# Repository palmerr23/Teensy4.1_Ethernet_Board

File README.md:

# Teensy4.1_Ethernet_Board
A HandRun HR91105A MagJack board for Teensy 4.1 Ethernet

Board files are KiCAD 6.0

Gerbers should be OK for most PCB manufacturers. Note there are no ground planes.

The CASE pad should be connected to chassis ground, if one exists. Do not connect the CASE pad to Teensy GND. 

## Design is still to be tested (awaiting PCBs).

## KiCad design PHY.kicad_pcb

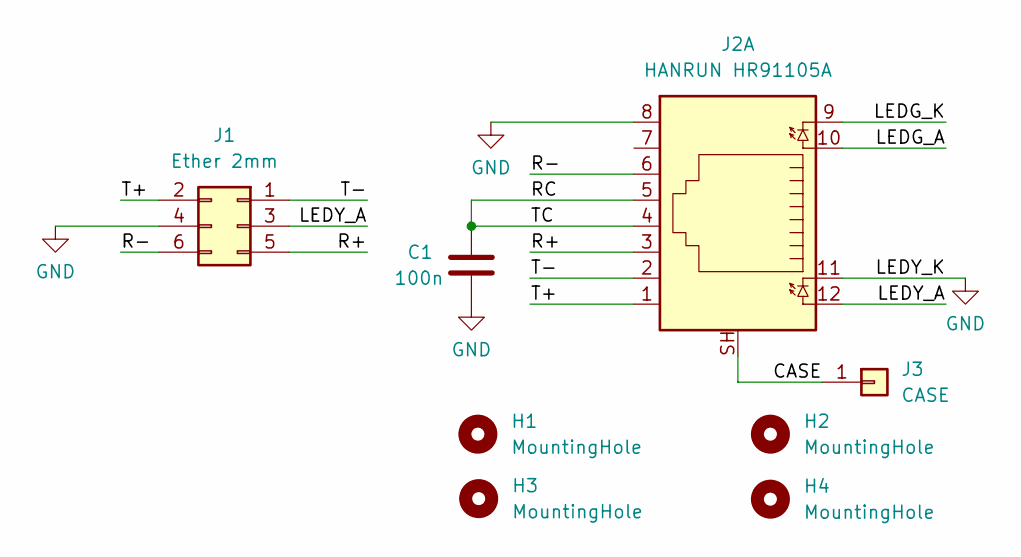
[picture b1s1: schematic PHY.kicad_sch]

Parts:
C1: 100n; C_0805_2012Metric_Pad1.18x1.45mm_HandSolder
H1, H2, H3, H4: MountingHole; MountingHole_3.5mm
J1: Ether 2mm; PinHeader_2x03_P2.00mm_Vertical
J2: HANRUN HR91105A; RJ45_Hanrun_HR911105A
J3: CASE; 1X01

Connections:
/CASE: J2.SH, J3.1
/LEDG_A: J2.10
/LEDG_K: J2.9
/LEDY_A: J1.3, J2.12
/R+: J1.5, J2.3
/R-: J1.6, J2.6
/RC: C1.1, J2.4, J2.5
/T+: J1.2, J2.1
/T-: J1.1, J2.2
GND: C1.2, J1.4, J2.8, J2.11

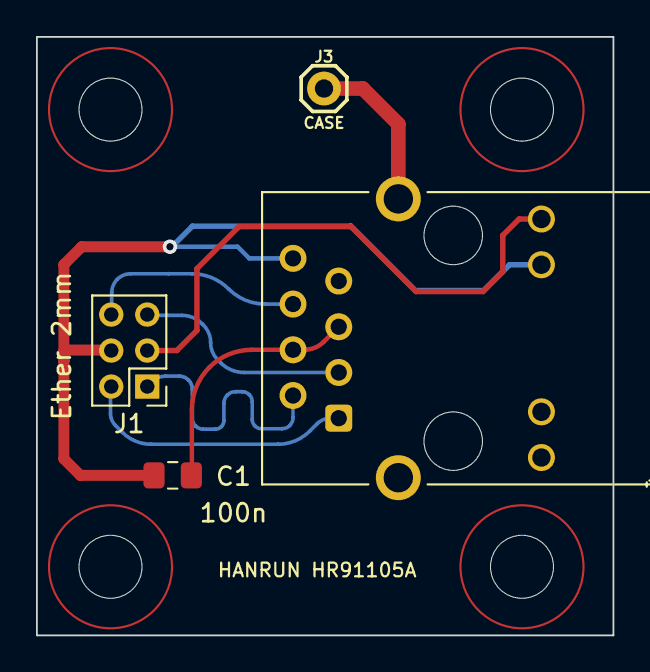
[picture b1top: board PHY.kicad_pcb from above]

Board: 2 copper layers, 32.0 x 33.2 mm, 8 parts (0 on the bottom side), 8 nets.
